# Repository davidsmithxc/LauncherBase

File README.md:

# LauncherBase
This is the source for all code in the launcher base.

The related overall project page can be found here.

The current design repo is online [here](https://cad.onshape.com/documents/31b609ea7c01403345c2da40/w/66efe11b5ed71e7d199776e8/e/5c5bedaf4e144ec01e841940).

TODO: Add project page

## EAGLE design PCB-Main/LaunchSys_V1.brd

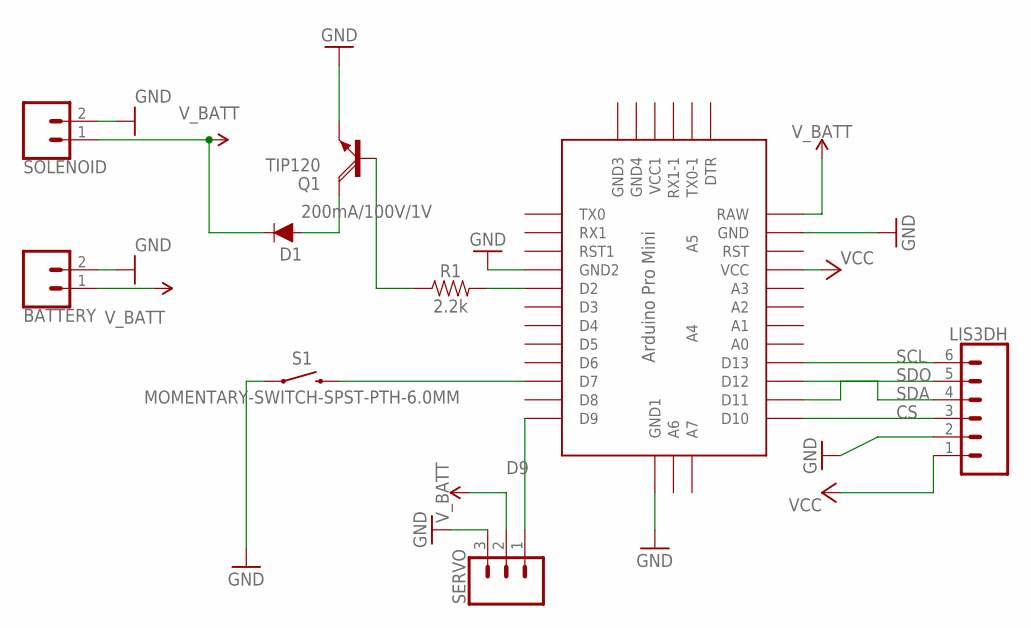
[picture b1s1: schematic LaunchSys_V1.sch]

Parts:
BATTERY: CONN_02; 1X02
D1: 200mA/100V/1V; DIODE-1N4148
LIS3DH: CONN_06SILK_FEMALE_PTH; 1X06
Q1: TIP120; TO220AH
R1: 2.2k; AXIAL-0.3
S1: MOMENTARY-SWITCH-SPST-PTH-6.0MM; TACTILE_SWITCH_PTH_6.0MM
SERVO: CONN_03; 1X03
SOLENOID: CONN_02; 1X02
U$1: ABK-PRO-MINI

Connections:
CS: LIS3DH.3, U$1.D10
D9: SERVO.1, U$1.D9
GND: BATTERY.2, LIS3DH.2, Q1.E, S1.1, SERVO.3, SOLENOID.2, U$1.GND, U$1.GND1 (GND2), U$1.GND4 (GND1)
unnamed: R1.P$2 (2), U$1.D2
unnamed: Q1.B, R1.P$1 (1)
unnamed: S1.3 (2), U$1.D7
unnamed: D1.A, Q1.C
SCL: LIS3DH.6, U$1.D13
SDA: LIS3DH.4, U$1.D12
SDO: LIS3DH.5, U$1.D11
VCC: LIS3DH.1, U$1.VCC
V_BATT: BATTERY.1, D1.C, SERVO.2, SOLENOID.1, U$1.RAW

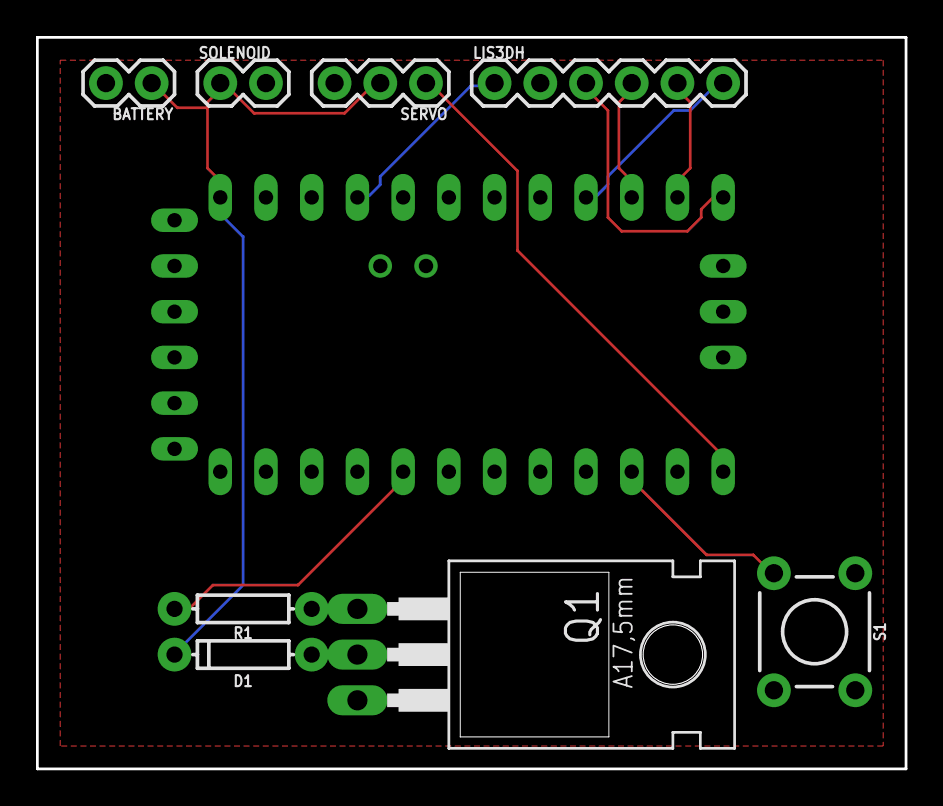
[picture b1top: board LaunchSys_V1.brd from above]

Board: 2 copper layers, 48.3 x 40.6 mm, 9 parts (0 on the bottom side), 12 nets.

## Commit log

2019-04-15 Updated launch board to include TIP120 power transistor and switch for controlling solenoid

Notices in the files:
parts and their libraries:
SparkFun-Connectors: Licensing: Creative Commons ShareAlike 4.0 International - https://creativecommons.org/licenses/by-sa/4.0
